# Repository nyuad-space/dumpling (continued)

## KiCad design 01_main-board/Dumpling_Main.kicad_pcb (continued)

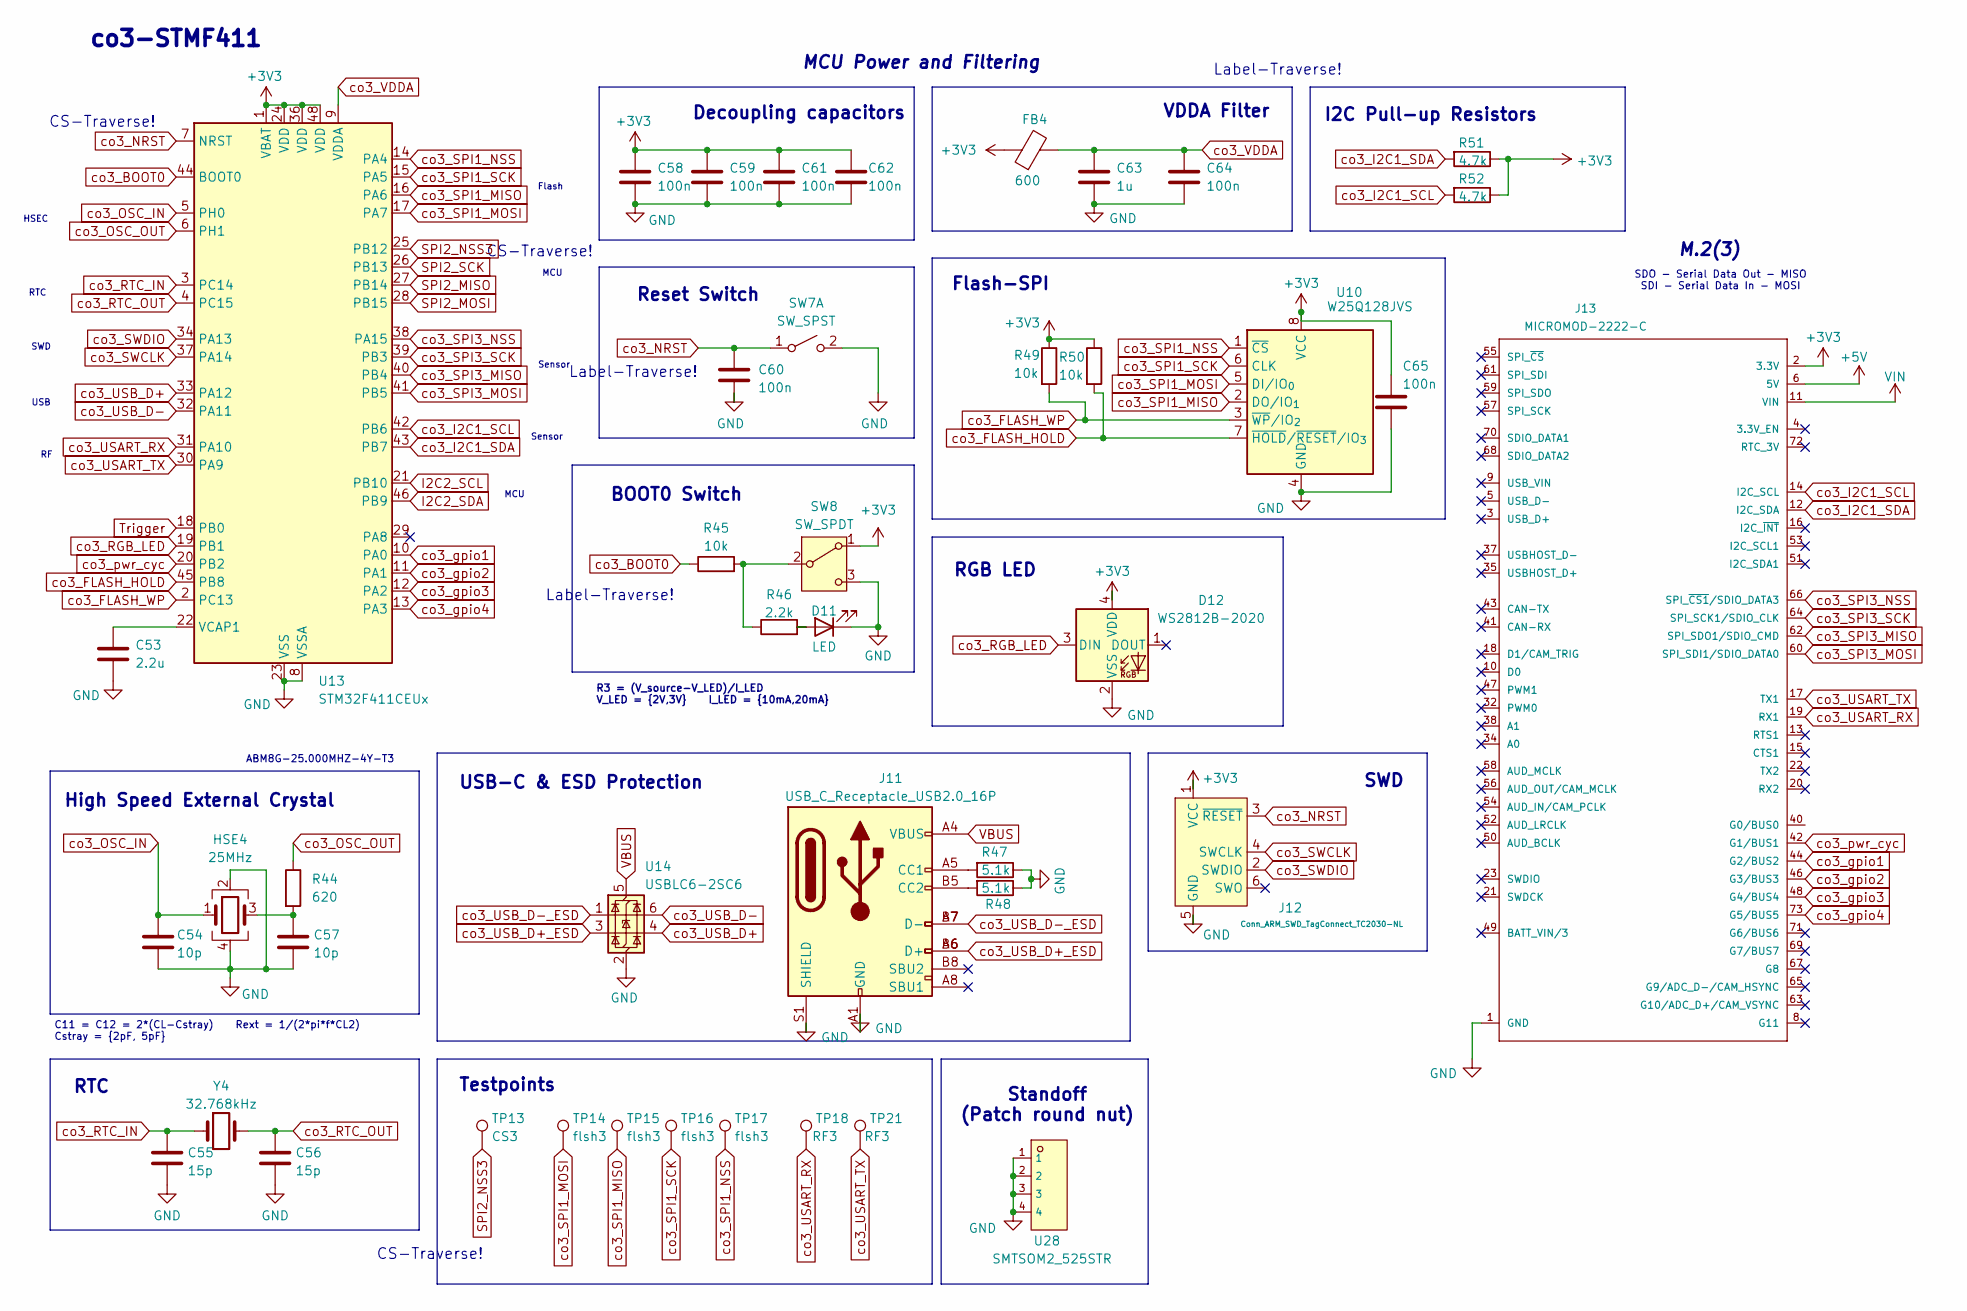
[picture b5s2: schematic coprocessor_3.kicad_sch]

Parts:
C53: 2.2u; C_0603_1608Metric
C54, C57: 10p; C_0402_1005Metric
C55, C56: 15p; C_0402_1005Metric
C58, C59, C60, C61, C62, C64, C65: 100n; C_0402_1005Metric
C63: 1u; C_0603_1608Metric
D11: LED; LED_0603_1608Metric
D12: WS2812B-2020; LED_WS2812B-2020_PLCC4_2.0x2.0mm
FB4: 600; L_0402_1005Metric
HSE4: 25MHz; Crystal_SMD_Abracon_ABM8G-4Pin_3.2x2.5mm
J11: USB_C_Receptacle_USB2.0_16P; USB_C_Receptacle_G-Switch_GT-USB-7051x
J12: Conn_ARM_SWD_TagConnect_TC2030-NL; Tag-Connect_TC2030-IDC-NL_2x03_P1.27mm_Vertical
J13: MICROMOD-2222-C; TE_2199119-4
R44: 620; R_0402_1005Metric
R45, R49, R50: 10k; R_0402_1005Metric
R46: 2.2k; R_0603_1608Metric
R47, R48: 5.1k; R_0402_1005Metric
R51, R52: 4.7k; R_0402_1005Metric
SW7: SW_SPST; SW_SPST_B3U-1000P
SW8: SW_SPDT; SW_JS102011JCQN
TP13: CS3; TestPoint_Pad_D1.0mm
TP14, TP15, TP16, TP17: flsh3; TestPoint_Pad_D1.0mm
TP18, TP21: RF3; TestPoint_Pad_D1.0mm
U10: W25Q128JVS; SOIC-8_5.3x5.3mm_P1.27mm
U13: STM32F411CEUx; QFN-48-1EP_7x7mm_P0.5mm_EP5.6x5.6mm
U14: USBLC6-2SC6; SOT-23-6
U28: SMTSOM2_525STR; SMD_BD5.6-D4.1; LCSC C22368605
Y4: 32.768kHz; Crystal_SMD_3215-2Pin_3.2x1.5mm

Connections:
+5V: J13.6 (5V); also elsewhere on the board
I2C2_SCL: U13.21 (PB10); also elsewhere on the board
I2C2_SDA: U13.46 (PB9); also elsewhere on the board
unnamed: C57.1, HSE4.3, R44.2
unnamed: D11.2 (A), R46.2
unnamed: J11.A5 (CC1), R47.2
unnamed: J11.B5 (CC2), R48.2
unnamed: R45.2, R46.1, SW8.2 (B)
unnamed: C53.1, U13.22 (VCAP1)
SPI2_MISO: U13.27 (PB14); also elsewhere on the board
SPI2_MOSI: U13.28 (PB15); also elsewhere on the board
SPI2_NSS3: TP13.1, U13.25 (PB12); also elsewhere on the board
SPI2_SCK: U13.26 (PB13); also elsewhere on the board
Trigger: U13.18 (PB0); also elsewhere on the board
VBUS: J11.A4 (VBUS), J11.A9 (VBUS), J11.B4 (VBUS), J11.B9 (VBUS), U14.5 (VBUS); also elsewhere on the board
VIN: J13.11 (VIN); also elsewhere on the board
co3_BOOT0: R45.1, U13.44 (BOOT0)
co3_FLASH_HOLD: R50.2, U10.7 (~HOLD/~RESET/IO_{3}), U13.45 (PB8)
co3_FLASH_WP: R49.2, U10.3 (~WP/IO_{2}), U13.2 (PC13)
co3_I2C1_SCL: J13.14 (I2C_SCL), R52.2, U13.42 (PB6)
co3_I2C1_SDA: J13.12 (I2C_SDA), R51.2, U13.43 (PB7)
co3_NRST: C60.1, J12.3 (~RESET), SW7.1 (A), U13.7 (NRST); also elsewhere on the board
co3_OSC_IN: C54.1, HSE4.1, U13.5 (PH0)
co3_OSC_OUT: R44.1, U13.6 (PH1)
co3_RGB_LED: D12.3 (DIN), U13.19 (PB1)
co3_RTC_IN: C55.1, U13.3 (PC14), Y4.1
co3_RTC_OUT: C56.1, U13.4 (PC15), Y4.2
co3_SPI1_MISO: TP15.1, U10.2 (DO/IO_{1}), U13.16 (PA6)
co3_SPI1_MOSI: TP14.1, U10.5 (DI/IO_{0}), U13.17 (PA7)
co3_SPI1_NSS: TP17.1, U10.1 (~CS), U13.14 (PA4)
co3_SPI1_SCK: TP16.1, U10.6 (CLK), U13.15 (PA5)
co3_SPI3_MISO: J13.62 (SPI_SDO1/SDIO_CMD), U13.40 (PB4)
co3_SPI3_MOSI: J13.60 (SPI_SDI1/SDIO_DATA0), U13.41 (PB5)
co3_SPI3_NSS: J13.66 (SPI_~CS1/SDIO_DATA3), U13.38 (PA15)
co3_SPI3_SCK: J13.64 (SPI_SCK1/SDIO_CLK), U13.39 (PB3)
co3_SWCLK: J12.4 (SWCLK), U13.37 (PA14)
co3_SWDIO: J12.2 (SWDIO), U13.34 (PA13)
co3_USART_RX: J13.19 (RX1), TP18.1, U13.31 (PA10)
co3_USART_TX: J13.17 (TX1), TP21.1, U13.30 (PA9)
co3_USB_D+: U13.33 (PA12), U14.4 (I/O2)
co3_USB_D+_ESD: J11.A6 (D+), J11.B6 (D+), U14.3 (I/O2)
co3_USB_D-: U13.32 (PA11), U14.6 (I/O1)
co3_USB_D-_ESD: J11.A7 (D-), J11.B7 (D-), U14.1 (I/O1)
co3_VDDA: C63.1, C64.1, FB4.2, U13.9 (VDDA)
co3_gpio1: J13.44 (G2/BUS2), U13.10 (PA0)
co3_gpio2: J13.46 (G3/BUS3), U13.11 (PA1)
co3_gpio3: J13.48 (G4/BUS4), U13.12 (PA2)
co3_gpio4: J13.73 (G5/BUS5), U13.13 (PA3)
co3_pwr_cyc: J13.42 (G1/BUS1), U13.20 (PB2)

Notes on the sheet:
Sensor
co3-STMF411
USB
Label-Traverse!
CS-Traverse!
SWD
Decoupling capacitors
Testpoints
C11 = C12 = 2*(CL-Cstray) Rext = 1/(2*pi*f*CL2) Cstray = {2pF, 5pF}
HSEC
Flash-SPI
BOOT0 Switch
Reset Switch
I2C Pull-up Resistors
VDDA Filter
High Speed External Crystal
M.2(3)
Standoff (Patch round nut)
SWD
Flash
MCU
RGB LED
ABM8G-25.000MHZ-4Y-T3
MCU Power and Filtering
SDO - Serial Data Out - MISO SDI - Serial Data In - MOSI
R3 = (V_source-V_LED)/I_LED V_LED = {2V,3V} I_LED = {10mA,20mA}
RTC
RTC
USB-C & ESD Protection

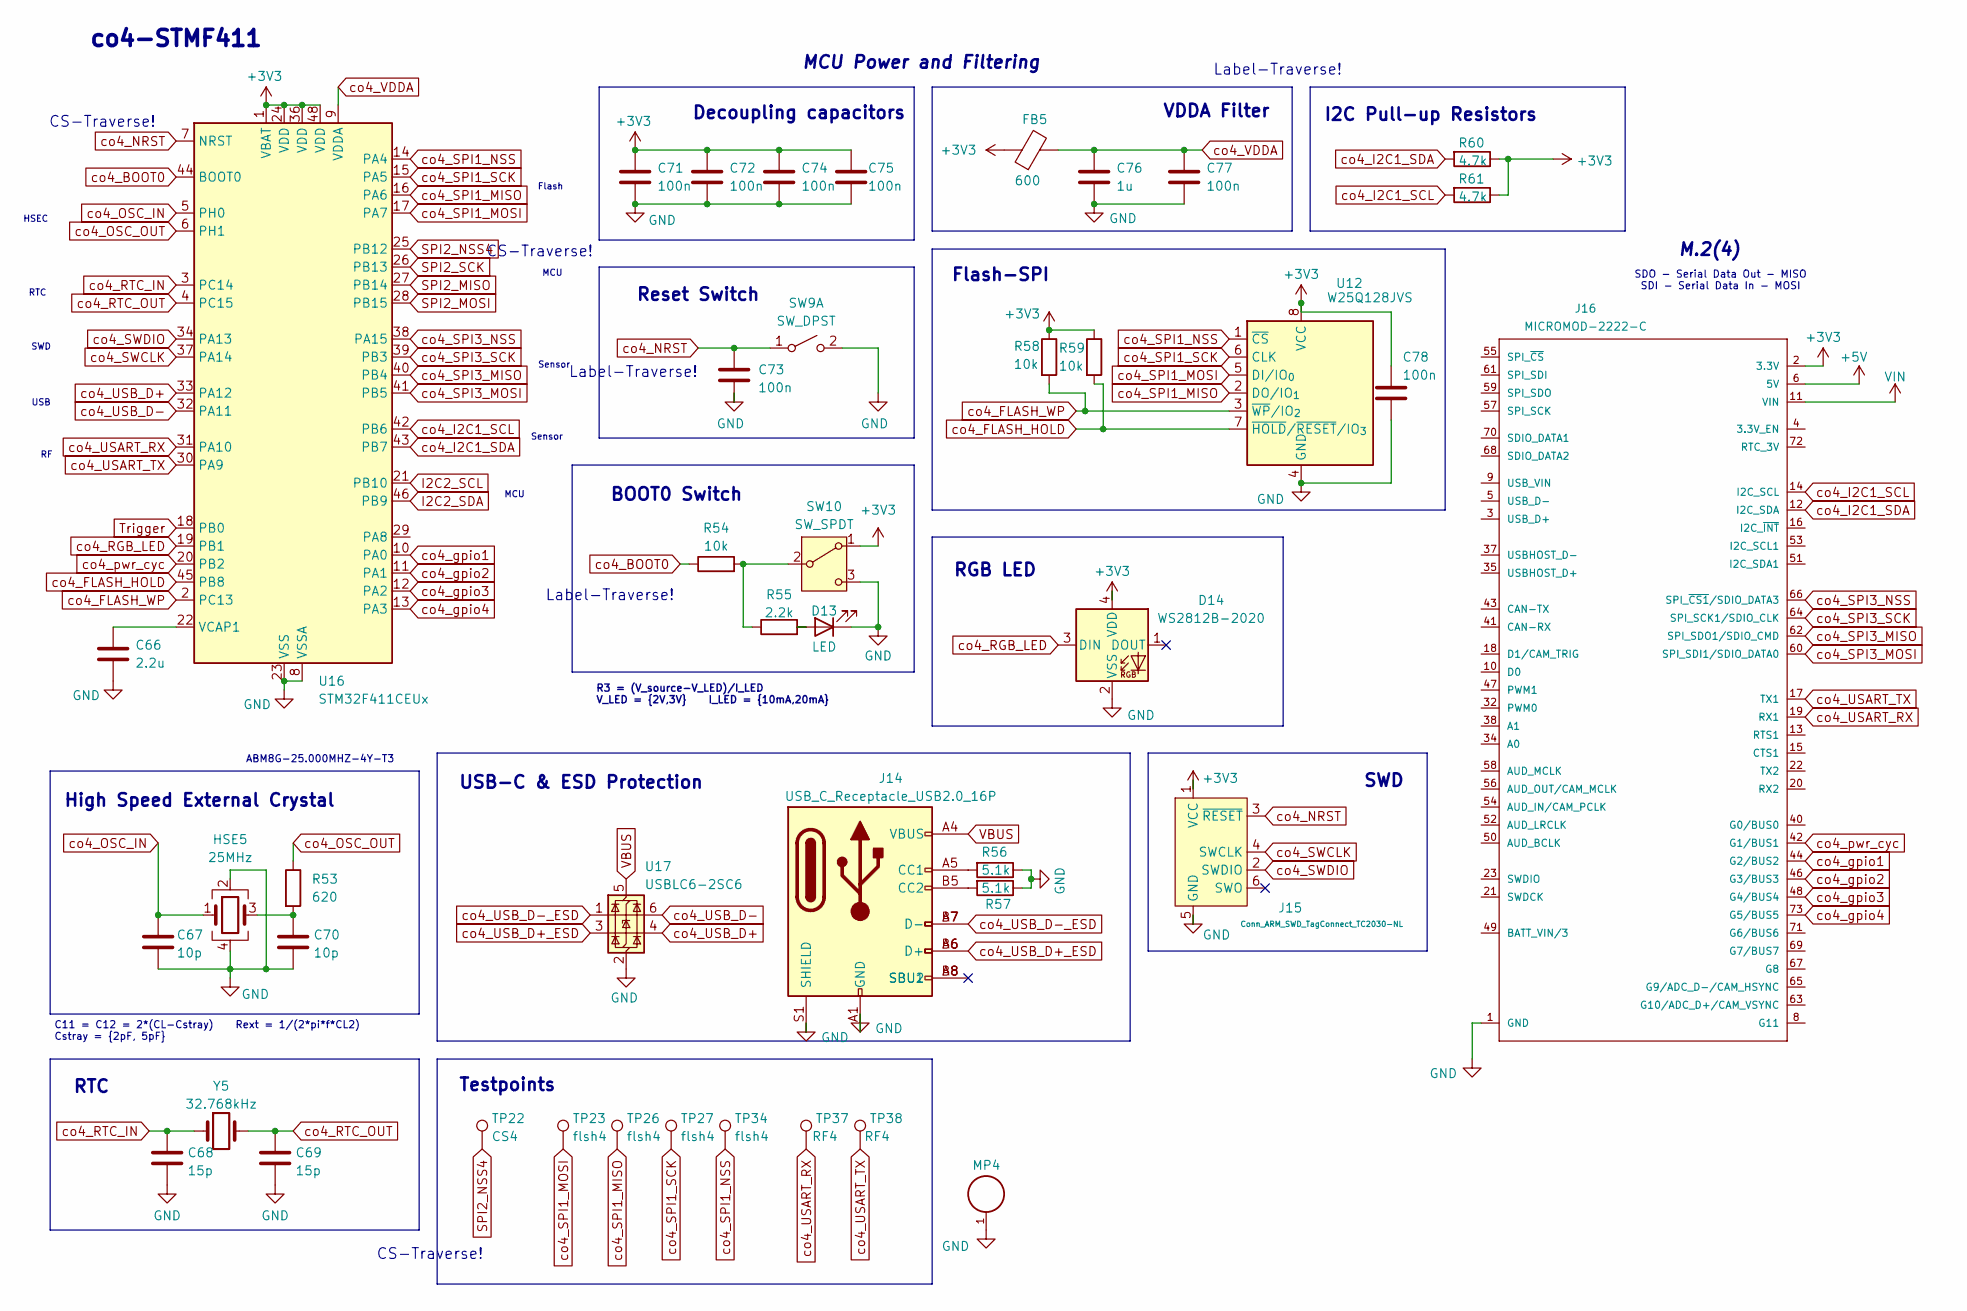
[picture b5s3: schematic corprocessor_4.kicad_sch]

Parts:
C66: 2.2u; C_0603_1608Metric
C67, C70: 10p; C_0402_1005Metric
C68, C69: 15p; C_0402_1005Metric
C71, C72, C73, C74, C75, C77, C78: 100n; C_0402_1005Metric
C76: 1u; C_0603_1608Metric
D13: LED; LED_0603_1608Metric
D14: WS2812B-2020; LED_WS2812B-2020_PLCC4_2.0x2.0mm
FB5: 600; L_0402_1005Metric
HSE5: 25MHz; Crystal_SMD_Abracon_ABM8G-4Pin_3.2x2.5mm
J14: USB_C_Receptacle_USB2.0_16P; USB_C_Receptacle_G-Switch_GT-USB-7051x
J15: Conn_ARM_SWD_TagConnect_TC2030-NL; Tag-Connect_TC2030-IDC-NL_2x03_P1.27mm_Vertical
J16: MICROMOD-2222-C; TE_2199119-4
MP4: WA-SMSI_9774025151; PART-NUMBER 9774025151R
R53: 620; R_0402_1005Metric
R54, R58, R59: 10k; R_0402_1005Metric
R55: 2.2k; R_0603_1608Metric
R56, R57: 5.1k; R_0402_1005Metric
R60, R61: 4.7k; R_0402_1005Metric
SW9: SW_DPST; SW_SPST_B3U-1000P
SW10: SW_SPDT; SW_CJS-1200TA
TP22: CS4; TestPoint_Pad_D1.0mm
TP23, TP26, TP27, TP34: flsh4; TestPoint_Pad_D1.0mm
TP37, TP38: RF4; TestPoint_Pad_D1.0mm
U12: W25Q128JVS; SOIC-8_5.3x5.3mm_P1.27mm
U16: STM32F411CEUx; QFN-48-1EP_7x7mm_P0.5mm_EP5.6x5.6mm
U17: USBLC6-2SC6; SOT-23-6
Y5: 32.768kHz; Crystal_SMD_3215-2Pin_3.2x1.5mm

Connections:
+5V: J16.6 (5V); also elsewhere on the board
I2C2_SCL: U16.21 (PB10); also elsewhere on the board
I2C2_SDA: U16.46 (PB9); also elsewhere on the board
unnamed: C70.1, HSE5.3, R53.2
unnamed: D13.2 (A), R55.2
unnamed: J14.A5 (CC1), R56.2
unnamed: J14.B5 (CC2), R57.2
unnamed: R54.2, R55.1, SW10.2 (B)
unnamed: C66.1, U16.22 (VCAP1)
SPI2_MISO: U16.27 (PB14); also elsewhere on the board
SPI2_MOSI: U16.28 (PB15); also elsewhere on the board
SPI2_NSS4: TP22.1, U16.25 (PB12); also elsewhere on the board
SPI2_SCK: U16.26 (PB13); also elsewhere on the board
Trigger: U16.18 (PB0); also elsewhere on the board
VBUS: J14.A4 (VBUS), J14.A9 (VBUS), J14.B4 (VBUS), J14.B9 (VBUS), U17.5 (VBUS); also elsewhere on the board
VIN: J16.11 (VIN); also elsewhere on the board
co4_BOOT0: R54.1, U16.44 (BOOT0)
co4_FLASH_HOLD: R59.2, U12.7 (~HOLD/~RESET/IO_{3}), U16.45 (PB8)
co4_FLASH_WP: R58.2, U12.3 (~WP/IO_{2}), U16.2 (PC13)
co4_I2C1_SCL: J16.14 (I2C_SCL), R61.2, U16.42 (PB6)
co4_I2C1_SDA: J16.12 (I2C_SDA), R60.2, U16.43 (PB7)
co4_NRST: C73.1, J15.3 (~RESET), SW9.1 (A), U16.7 (NRST); also elsewhere on the board
co4_OSC_IN: C67.1, HSE5.1, U16.5 (PH0)
co4_OSC_OUT: R53.1, U16.6 (PH1)
co4_RGB_LED: D14.3 (DIN), U16.19 (PB1)
co4_RTC_IN: C68.1, U16.3 (PC14), Y5.1
co4_RTC_OUT: C69.1, U16.4 (PC15), Y5.2
co4_SPI1_MISO: TP26.1, U12.2 (DO/IO_{1}), U16.16 (PA6)
co4_SPI1_MOSI: TP23.1, U12.5 (DI/IO_{0}), U16.17 (PA7)
co4_SPI1_NSS: TP34.1, U12.1 (~CS), U16.14 (PA4)
co4_SPI1_SCK: TP27.1, U12.6 (CLK), U16.15 (PA5)
co4_SPI3_MISO: J16.62 (SPI_SDO1/SDIO_CMD), U16.40 (PB4)
co4_SPI3_MOSI: J16.60 (SPI_SDI1/SDIO_DATA0), U16.41 (PB5)
co4_SPI3_NSS: J16.66 (SPI_~CS1/SDIO_DATA3), U16.38 (PA15)
co4_SPI3_SCK: J16.64 (SPI_SCK1/SDIO_CLK), U16.39 (PB3)
co4_SWCLK: J15.4 (SWCLK), U16.37 (PA14)
co4_SWDIO: J15.2 (SWDIO), U16.34 (PA13)
co4_USART_RX: J16.19 (RX1), TP37.1, U16.31 (PA10)
co4_USART_TX: J16.17 (TX1), TP38.1, U16.30 (PA9)
co4_USB_D+: U16.33 (PA12), U17.4 (I/O2)
co4_USB_D+_ESD: J14.A6 (D+), J14.B6 (D+), U17.3 (I/O2)
co4_USB_D-: U16.32 (PA11), U17.6 (I/O1)
co4_USB_D-_ESD: J14.A7 (D-), J14.B7 (D-), U17.1 (I/O1)
co4_VDDA: C76.1, C77.1, FB5.2, U16.9 (VDDA)
co4_gpio1: J16.44 (G2/BUS2), U16.10 (PA0)
co4_gpio2: J16.46 (G3/BUS3), U16.11 (PA1)
co4_gpio3: J16.48 (G4/BUS4), U16.12 (PA2)
co4_gpio4: J16.73 (G5/BUS5), U16.13 (PA3)
co4_pwr_cyc: J16.42 (G1/BUS1), U16.20 (PB2)

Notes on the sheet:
MCU
RTC
Testpoints
USB
Sensor
M.2(4)
USB-C & ESD Protection
HSEC
MCU Power and Filtering
Label-Traverse!
VDDA Filter
RTC
RGB LED
I2C Pull-up Resistors
C11 = C12 = 2*(CL-Cstray) Rext = 1/(2*pi*f*CL2) Cstray = {2pF, 5pF}
co4-STMF411
Flash
Reset Switch
R3 = (V_source-V_LED)/I_LED V_LED = {2V,3V} I_LED = {10mA,20mA}
CS-Traverse!
SWD
BOOT0 Switch
ABM8G-25.000MHZ-4Y-T3
SDO - Serial Data Out - MISO SDI - Serial Data In - MOSI
Decoupling capacitors
Flash-SPI
High Speed External Crystal
SWD

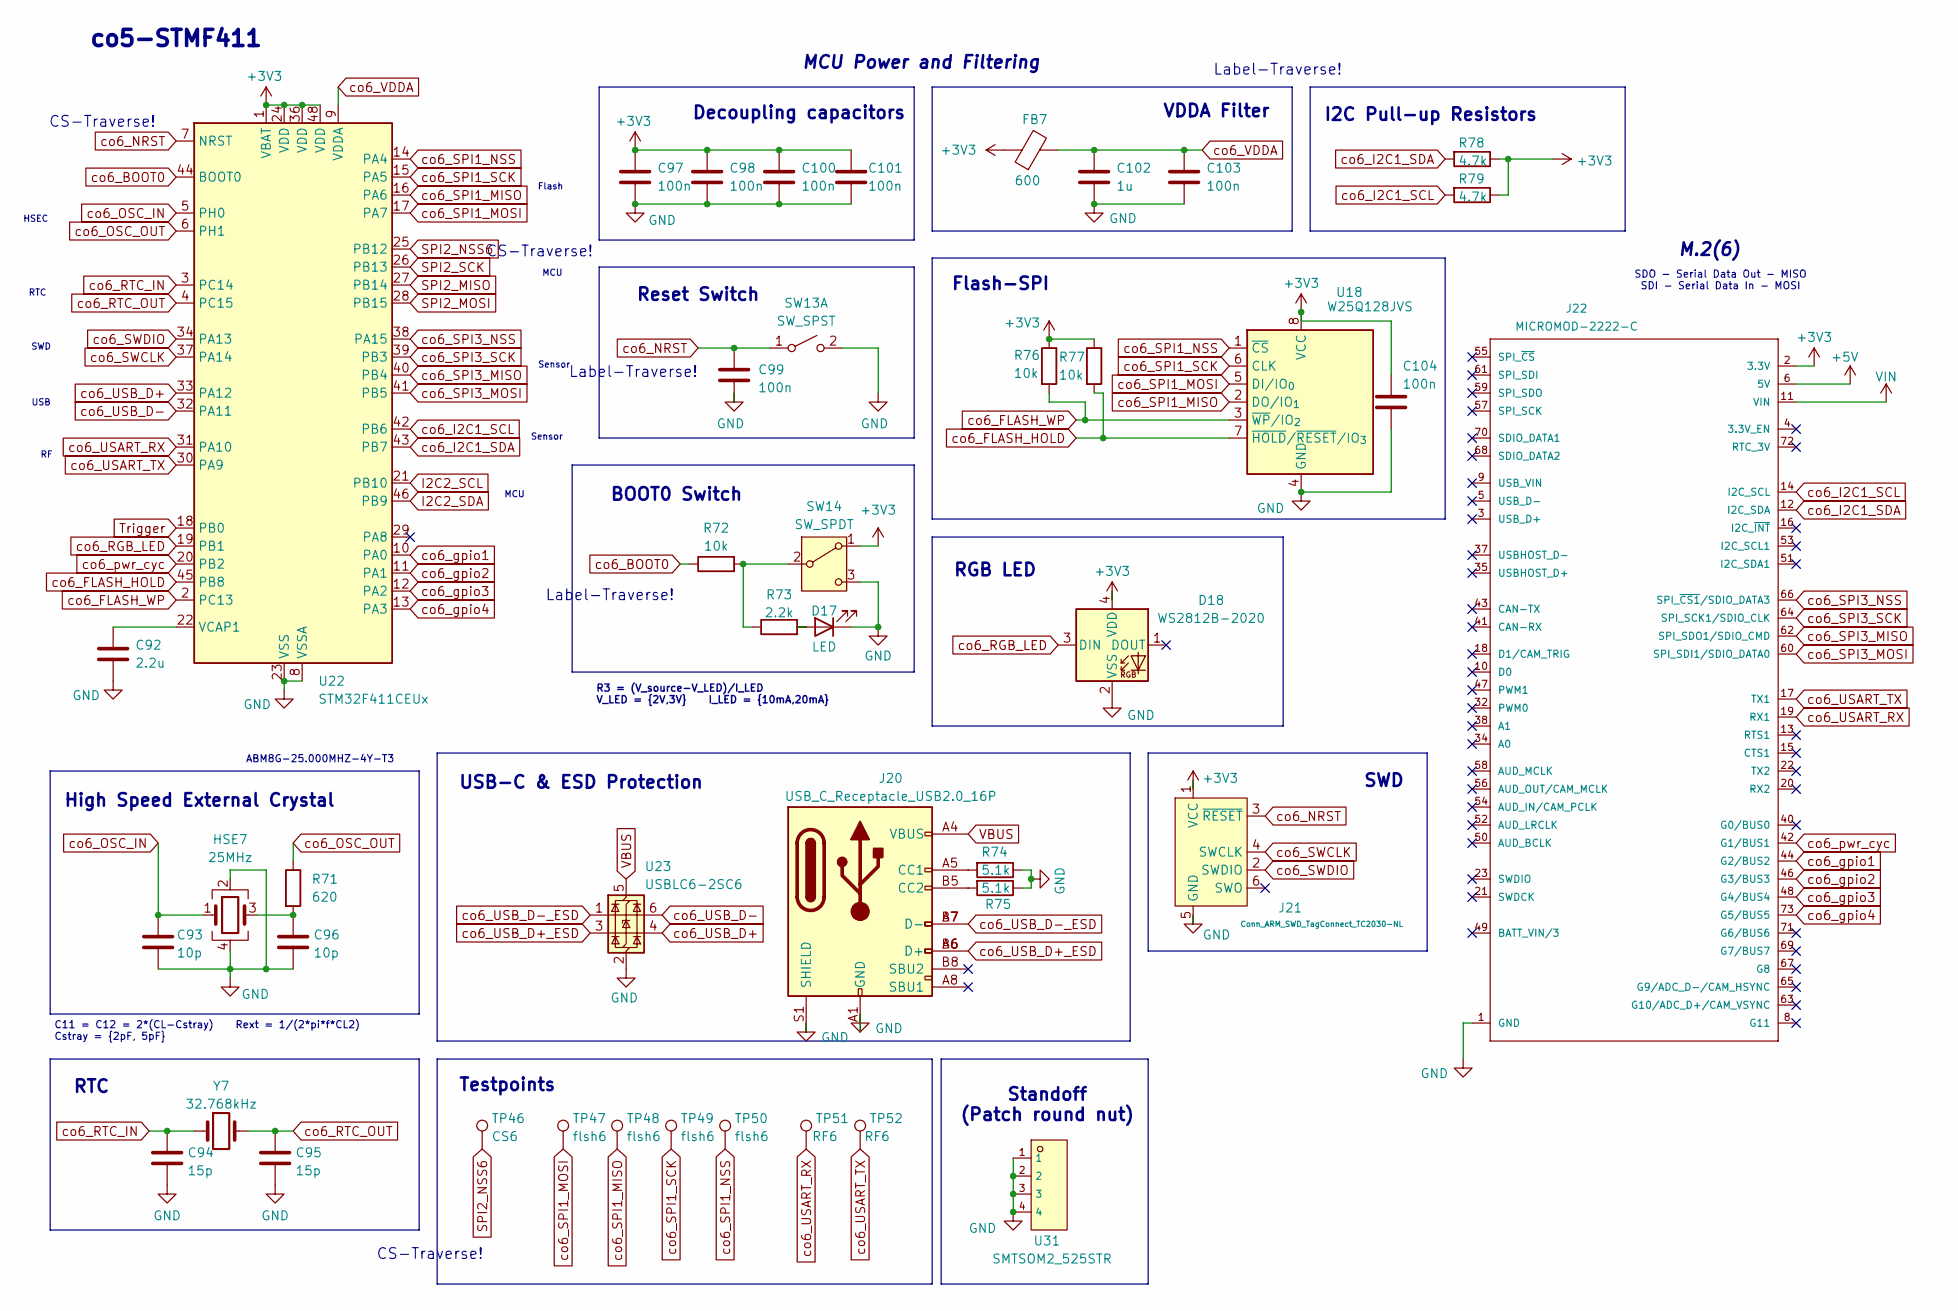
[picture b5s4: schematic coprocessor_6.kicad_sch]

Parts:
C92: 2.2u; C_0603_1608Metric
C93, C96: 10p; C_0402_1005Metric
C94, C95: 15p; C_0402_1005Metric
C97, C98, C99, C100, C101, C103, C104: 100n; C_0402_1005Metric
C102: 1u; C_0603_1608Metric
D17: LED; LED_0603_1608Metric
D18: WS2812B-2020; LED_WS2812B-2020_PLCC4_2.0x2.0mm
FB7: 600; L_0402_1005Metric
HSE7: 25MHz; Crystal_SMD_Abracon_ABM8G-4Pin_3.2x2.5mm
J20: USB_C_Receptacle_USB2.0_16P; USB_C_Receptacle_G-Switch_GT-USB-7051x
J21: Conn_ARM_SWD_TagConnect_TC2030-NL; Tag-Connect_TC2030-IDC-NL_2x03_P1.27mm_Vertical
J22: MICROMOD-2222-C; TE_2199119-4
R71: 620; R_0402_1005Metric
R72, R76, R77: 10k; R_0402_1005Metric
R73: 2.2k; R_0603_1608Metric
R74, R75: 5.1k; R_0402_1005Metric
R78, R79: 4.7k; R_0402_1005Metric
SW13: SW_SPST; SW_SPST_B3U-1000P
SW14: SW_SPDT; SW_JS102011JCQN
TP46: CS6; TestPoint_Pad_D1.0mm
TP47, TP48, TP49, TP50: flsh6; TestPoint_Pad_D1.0mm
TP51, TP52: RF6; TestPoint_Pad_D1.0mm
U18: W25Q128JVS; SOIC-8_5.3x5.3mm_P1.27mm
U22: STM32F411CEUx; QFN-48-1EP_7x7mm_P0.5mm_EP5.6x5.6mm
U23: USBLC6-2SC6; SOT-23-6
U31: SMTSOM2_525STR; SMD_BD5.6-D4.1; LCSC C22368605
Y7: 32.768kHz; Crystal_SMD_3215-2Pin_3.2x1.5mm

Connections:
+5V: J22.6 (5V); also elsewhere on the board
I2C2_SCL: U22.21 (PB10); also elsewhere on the board
I2C2_SDA: U22.46 (PB9); also elsewhere on the board
unnamed: C96.1, HSE7.3, R71.2
unnamed: D17.2 (A), R73.2
unnamed: J20.A5 (CC1), R74.2
unnamed: J20.B5 (CC2), R75.2
unnamed: R72.2, R73.1, SW14.2 (B)
unnamed: C92.1, U22.22 (VCAP1)
SPI2_MISO: U22.27 (PB14); also elsewhere on the board
SPI2_MOSI: U22.28 (PB15); also elsewhere on the board
SPI2_NSS6: TP46.1, U22.25 (PB12); also elsewhere on the board
SPI2_SCK: U22.26 (PB13); also elsewhere on the board
Trigger: U22.18 (PB0); also elsewhere on the board
VBUS: J20.A4 (VBUS), J20.A9 (VBUS), J20.B4 (VBUS), J20.B9 (VBUS), U23.5 (VBUS); also elsewhere on the board
VIN: J22.11 (VIN); also elsewhere on the board
co6_BOOT0: R72.1, U22.44 (BOOT0)
co6_FLASH_HOLD: R77.2, U18.7 (~HOLD/~RESET/IO_{3}), U22.45 (PB8)
co6_FLASH_WP: R76.2, U18.3 (~WP/IO_{2}), U22.2 (PC13)
co6_I2C1_SCL: J22.14 (I2C_SCL), R79.2, U22.42 (PB6)
co6_I2C1_SDA: J22.12 (I2C_SDA), R78.2, U22.43 (PB7)
co6_NRST: C99.1, J21.3 (~RESET), SW13.1 (A), U22.7 (NRST); also elsewhere on the board
co6_OSC_IN: C93.1, HSE7.1, U22.5 (PH0)
co6_OSC_OUT: R71.1, U22.6 (PH1)
co6_RGB_LED: D18.3 (DIN), U22.19 (PB1)
co6_RTC_IN: C94.1, U22.3 (PC14), Y7.1
co6_RTC_OUT: C95.1, U22.4 (PC15), Y7.2
co6_SPI1_MISO: TP48.1, U18.2 (DO/IO_{1}), U22.16 (PA6)
co6_SPI1_MOSI: TP47.1, U18.5 (DI/IO_{0}), U22.17 (PA7)
co6_SPI1_NSS: TP50.1, U18.1 (~CS), U22.14 (PA4)
co6_SPI1_SCK: TP49.1, U18.6 (CLK), U22.15 (PA5)
co6_SPI3_MISO: J22.62 (SPI_SDO1/SDIO_CMD), U22.40 (PB4)
co6_SPI3_MOSI: J22.60 (SPI_SDI1/SDIO_DATA0), U22.41 (PB5)
co6_SPI3_NSS: J22.66 (SPI_~CS1/SDIO_DATA3), U22.38 (PA15)
co6_SPI3_SCK: J22.64 (SPI_SCK1/SDIO_CLK), U22.39 (PB3)
co6_SWCLK: J21.4 (SWCLK), U22.37 (PA14)
co6_SWDIO: J21.2 (SWDIO), U22.34 (PA13)
co6_USART_RX: J22.19 (RX1), TP51.1, U22.31 (PA10)
co6_USART_TX: J22.17 (TX1), TP52.1, U22.30 (PA9)
co6_USB_D+: U22.33 (PA12), U23.4 (I/O2)
co6_USB_D+_ESD: J20.A6 (D+), J20.B6 (D+), U23.3 (I/O2)
co6_USB_D-: U22.32 (PA11), U23.6 (I/O1)
co6_USB_D-_ESD: J20.A7 (D-), J20.B7 (D-), U23.1 (I/O1)
co6_VDDA: C102.1, C103.1, FB7.2, U22.9 (VDDA)
co6_gpio1: J22.44 (G2/BUS2), U22.10 (PA0)
co6_gpio2: J22.46 (G3/BUS3), U22.11 (PA1)
co6_gpio3: J22.48 (G4/BUS4), U22.12 (PA2)
co6_gpio4: J22.73 (G5/BUS5), U22.13 (PA3)
co6_pwr_cyc: J22.42 (G1/BUS1), U22.20 (PB2)

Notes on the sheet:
R3 = (V_source-V_LED)/I_LED V_LED = {2V,3V} I_LED = {10mA,20mA}
HSEC
USB-C & ESD Protection
ABM8G-25.000MHZ-4Y-T3
C11 = C12 = 2*(CL-Cstray) Rext = 1/(2*pi*f*CL2) Cstray = {2pF, 5pF}
Sensor
Label-Traverse!
BOOT0 Switch
SDO - Serial Data Out - MISO SDI - Serial Data In - MOSI
CS-Traverse!
Decoupling capacitors
Reset Switch
Flash
MCU
USB
RGB LED
High Speed External Crystal
SWD
co5-STMF411
I2C Pull-up Resistors
VDDA Filter
M.2(6)
RTC
MCU Power and Filtering
Standoff (Patch round nut)
Flash-SPI
SWD
Testpoints
RTC

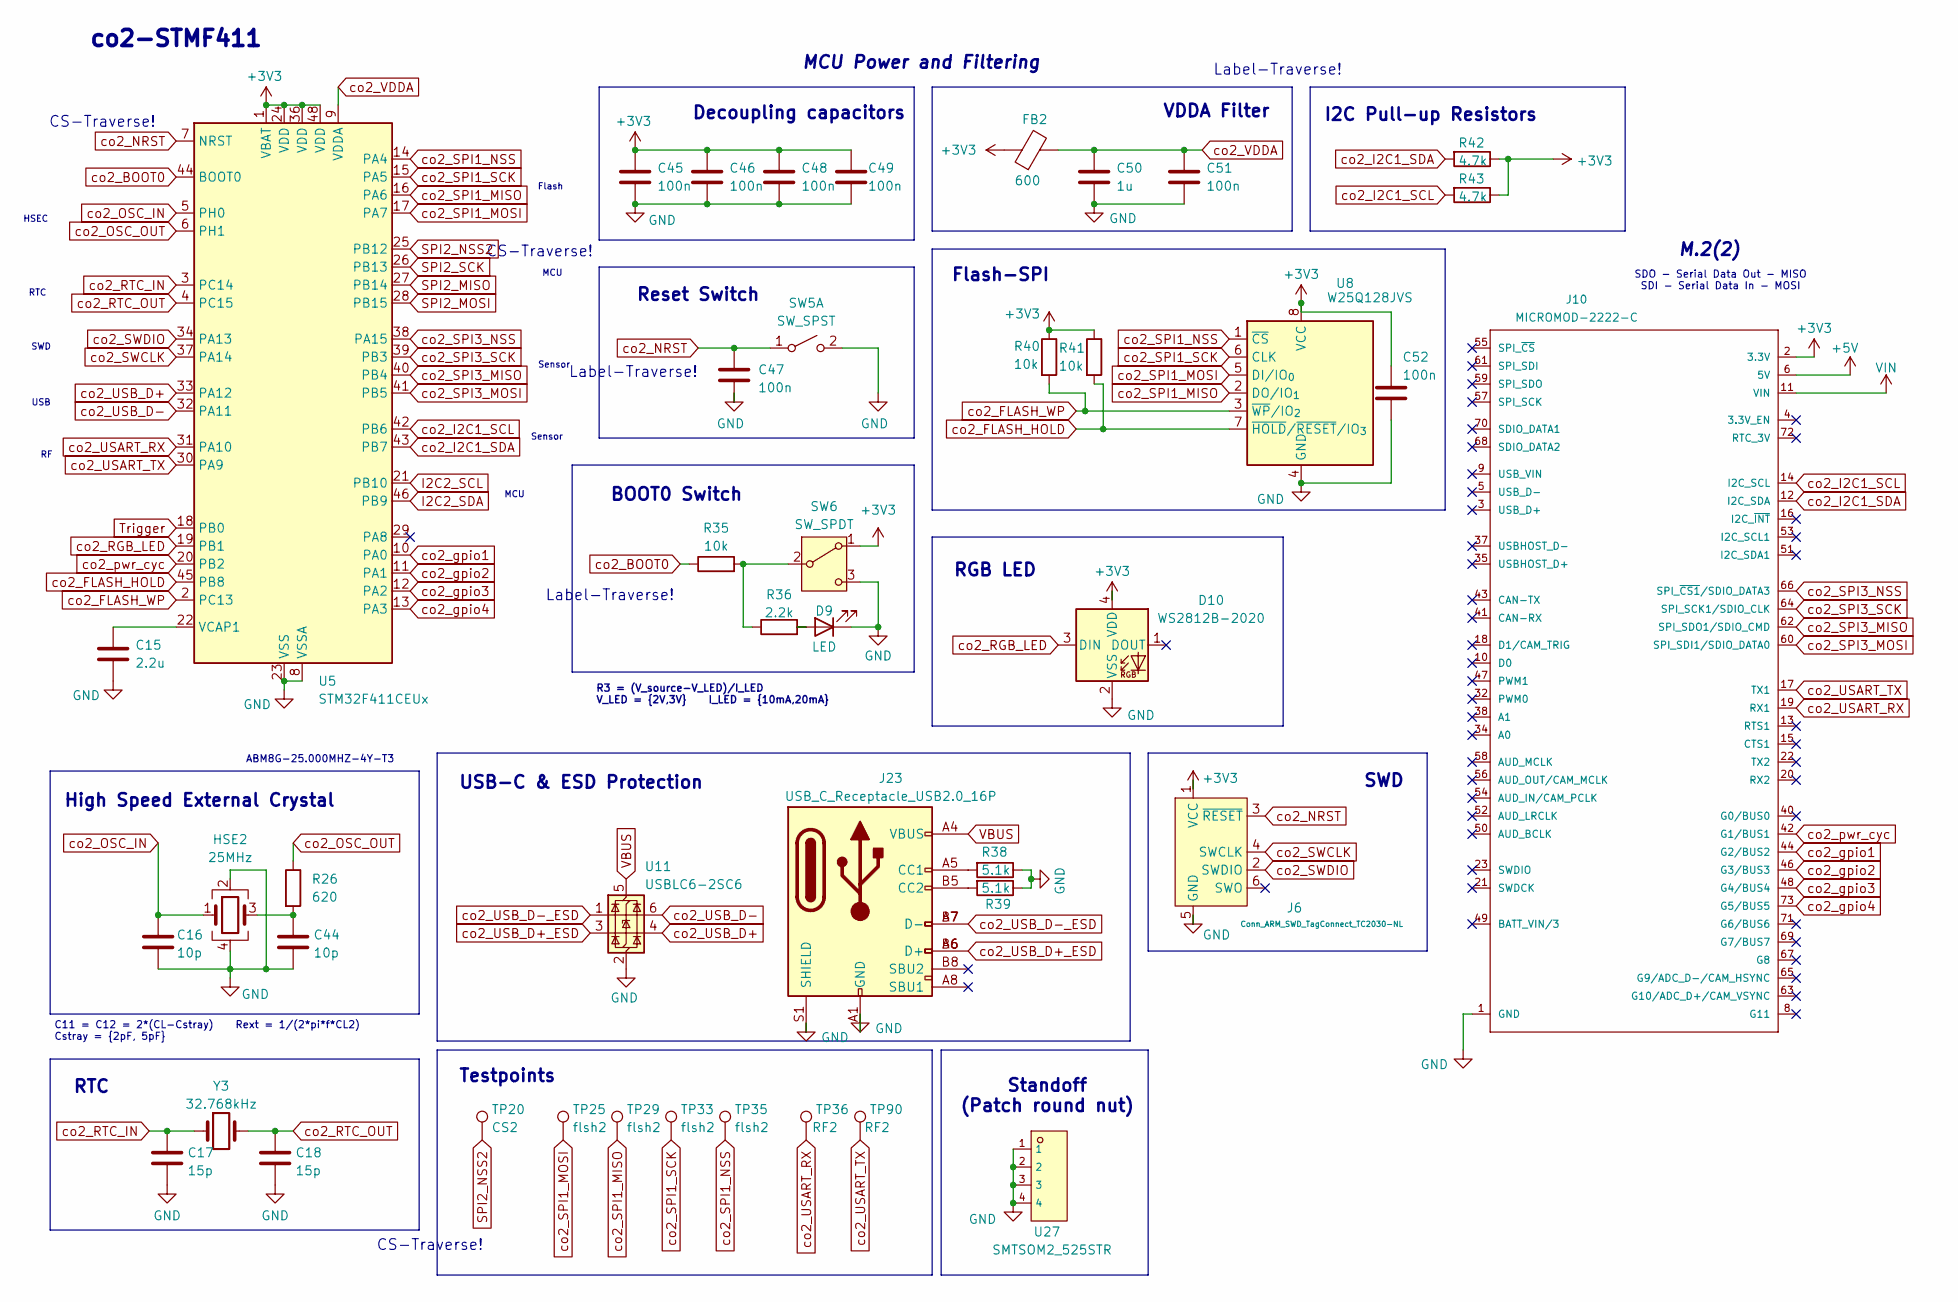
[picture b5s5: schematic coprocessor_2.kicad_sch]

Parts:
C15: 2.2u; C_0603_1608Metric
C16, C44: 10p; C_0402_1005Metric
C17, C18: 15p; C_0402_1005Metric
C45, C46, C47, C48, C49, C51, C52: 100n; C_0402_1005Metric
C50: 1u; C_0603_1608Metric
D9: LED; LED_0603_1608Metric
D10: WS2812B-2020; LED_WS2812B-2020_PLCC4_2.0x2.0mm
FB2: 600; L_0402_1005Metric
HSE2: 25MHz; Crystal_SMD_Abracon_ABM8G-4Pin_3.2x2.5mm
J6: Conn_ARM_SWD_TagConnect_TC2030-NL; Tag-Connect_TC2030-IDC-NL_2x03_P1.27mm_Vertical
J10: MICROMOD-2222-C; TE_2199119-4
J23: USB_C_Receptacle_USB2.0_16P; USB_C_Receptacle_G-Switch_GT-USB-7051x
R26: 620; R_0402_1005Metric
R35, R40, R41: 10k; R_0402_1005Metric
R36: 2.2k; R_0603_1608Metric
R38, R39: 5.1k; R_0402_1005Metric
R42, R43: 4.7k; R_0402_1005Metric
SW5: SW_SPST; SW_SPST_B3U-1000P
SW6: SW_SPDT; SW_JS102011JCQN
TP20: CS2; TestPoint_Pad_D1.0mm
TP25, TP29, TP33, TP35: flsh2; TestPoint_Pad_D1.0mm
TP36, TP90: RF2; TestPoint_Pad_D1.0mm
U5: STM32F411CEUx; QFN-48-1EP_7x7mm_P0.5mm_EP5.6x5.6mm
U8: W25Q128JVS; SOIC-8_5.3x5.3mm_P1.27mm
U11: USBLC6-2SC6; SOT-23-6
U27: SMTSOM2_525STR; SMD_BD5.6-D4.1; LCSC C22368605
Y3: 32.768kHz; Crystal_SMD_3215-2Pin_3.2x1.5mm

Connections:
+5V: J10.6 (5V); also elsewhere on the board
I2C2_SCL: U5.21 (PB10); also elsewhere on the board
I2C2_SDA: U5.46 (PB9); also elsewhere on the board
unnamed: C44.1, HSE2.3, R26.2
unnamed: D9.2 (A), R36.2
unnamed: J23.A5 (CC1), R38.2
unnamed: J23.B5 (CC2), R39.2
unnamed: R35.2, R36.1, SW6.2 (B)
unnamed: C15.1, U5.22 (VCAP1)
SPI2_MISO: U5.27 (PB14); also elsewhere on the board
SPI2_MOSI: U5.28 (PB15); also elsewhere on the board
SPI2_NSS2: TP20.1, U5.25 (PB12); also elsewhere on the board
SPI2_SCK: U5.26 (PB13); also elsewhere on the board
Trigger: U5.18 (PB0); also elsewhere on the board
VBUS: J23.A4 (VBUS), J23.A9 (VBUS), J23.B4 (VBUS), J23.B9 (VBUS), U11.5 (VBUS); also elsewhere on the board
VIN: J10.11 (VIN); also elsewhere on the board
co2_BOOT0: R35.1, U5.44 (BOOT0)
co2_FLASH_HOLD: R41.2, U5.45 (PB8), U8.7 (~HOLD/~RESET/IO_{3})
co2_FLASH_WP: R40.2, U5.2 (PC13), U8.3 (~WP/IO_{2})
co2_I2C1_SCL: J10.14 (I2C_SCL), R43.2, U5.42 (PB6)
co2_I2C1_SDA: J10.12 (I2C_SDA), R42.2, U5.43 (PB7)
co2_NRST: C47.1, J6.3 (~RESET), SW5.1 (A), U5.7 (NRST); also elsewhere on the board
co2_OSC_IN: C16.1, HSE2.1, U5.5 (PH0)
co2_OSC_OUT: R26.1, U5.6 (PH1)
co2_RGB_LED: D10.3 (DIN), U5.19 (PB1)
co2_RTC_IN: C17.1, U5.3 (PC14), Y3.1
co2_RTC_OUT: C18.1, U5.4 (PC15), Y3.2
co2_SPI1_MISO: TP29.1, U5.16 (PA6), U8.2 (DO/IO_{1})
co2_SPI1_MOSI: TP25.1, U5.17 (PA7), U8.5 (DI/IO_{0})
co2_SPI1_NSS: TP35.1, U5.14 (PA4), U8.1 (~CS)
co2_SPI1_SCK: TP33.1, U5.15 (PA5), U8.6 (CLK)
co2_SPI3_MISO: J10.62 (SPI_SDO1/SDIO_CMD), U5.40 (PB4)
co2_SPI3_MOSI: J10.60 (SPI_SDI1/SDIO_DATA0), U5.41 (PB5)
co2_SPI3_NSS: J10.66 (SPI_~CS1/SDIO_DATA3), U5.38 (PA15)
co2_SPI3_SCK: J10.64 (SPI_SCK1/SDIO_CLK), U5.39 (PB3)
co2_SWCLK: J6.4 (SWCLK), U5.37 (PA14)
co2_SWDIO: J6.2 (SWDIO), U5.34 (PA13)
co2_USART_RX: J10.19 (RX1), TP36.1, U5.31 (PA10)
co2_USART_TX: J10.17 (TX1), TP90.1, U5.30 (PA9)
co2_USB_D+: U5.33 (PA12), U11.4 (I/O2)
co2_USB_D+_ESD: J23.A6 (D+), J23.B6 (D+), U11.3 (I/O2)
co2_USB_D-: U5.32 (PA11), U11.6 (I/O1)
co2_USB_D-_ESD: J23.A7 (D-), J23.B7 (D-), U11.1 (I/O1)
co2_VDDA: C50.1, C51.1, FB2.2, U5.9 (VDDA)
co2_gpio1: J10.44 (G2/BUS2), U5.10 (PA0)
co2_gpio2: J10.46 (G3/BUS3), U5.11 (PA1)
co2_gpio3: J10.48 (G4/BUS4), U5.12 (PA2)
co2_gpio4: J10.73 (G5/BUS5), U5.13 (PA3)
co2_pwr_cyc: J10.42 (G1/BUS1), U5.20 (PB2)

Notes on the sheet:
Label-Traverse!
RGB LED
Sensor
USB
VDDA Filter
SWD
HSEC
C11 = C12 = 2*(CL-Cstray) Rext = 1/(2*pi*f*CL2) Cstray = {2pF, 5pF}
CS-Traverse!
High Speed External Crystal
USB-C & ESD Protection
Flash-SPI
Testpoints
Standoff (Patch round nut)
R3 = (V_source-V_LED)/I_LED V_LED = {2V,3V} I_LED = {10mA,20mA}
SWD
RTC
Flash
Decoupling capacitors
RTC
Reset Switch
MCU
ABM8G-25.000MHZ-4Y-T3
MCU Power and Filtering
co2-STMF411
BOOT0 Switch
SDO - Serial Data Out - MISO SDI - Serial Data In - MOSI
M.2(2)
I2C Pull-up Resistors

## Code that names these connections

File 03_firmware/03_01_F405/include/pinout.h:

// Interboard SPI pins
#define INTERBOARD_SPI_SCK PB13
#define INTERBOARD_SPI_MISO PB14
#define INTERBOARD_SPI_MOSI PB15

#define INTERBOARD_SPI_CO1_CS PC3
#define INTERBOARD_SPI_CO2_CS PB12
#define INTERBOARD_SPI_CO3_CS PC2
#define INTERBOARD_SPI_CO4_CS PC6
#define INTERBOARD_SPI_CO5_CS PC4
#define INTERBOARD_SPI_CO6_CS PC5


// Flash SPI pins
#define FLASH_SPI_CS PA4
#define FLASH_SPI_SCK PA5
#define FLASH_SPI_MISO PA6
#define FLASH_SPI_MOSI PA7

// Log triger
#define LOG_TRIGGER_GPIO PC13

// MPU Pins
#define MPU_SCL PA8
#define MPU_SDA PC9
#define MPU_INT PA8

// Indicators
#define BUZZER PB8
#define RGB_LED PB9

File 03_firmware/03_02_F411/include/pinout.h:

// SPI bus (SPI3)
// Use ALT1 pin names to avoid SPI conflict. 
// This guarantees SENSOR_SPI will use SPI3, as expected.
#define SENSOR_SCK PB3_ALT1
#define SENSOR_MISO PB4_ALT1  
#define SENSOR_MOSI PB5_ALT1

// Sensor CS
#define SENSOR_CS PA15
#define LSM6DS_CS PA15
#define DPS310_CS PA15
#define BMI088_Accel_CS PA15
#define BMI088_Gyro_CS PA2

// SPI bus (SPI2)
#define INTERBOARD_CS PB12 // Dummy
#define INTERBOARD_SCK PB13
#define INTERBOARD_MISO PB14
#define INTERBOARD_MOSI PB15

// SPI bus (SPI1)
#define FLASH_CS PA4
#define FLASH_SCK PA5
#define FLASH_MISO PA6
#define FLASH_MOSI PA7

// I2C sensors (I2C1)
#define SENSOR_SCL PB6
#define SENSOR_SDA PB7

// Log triger
#define LOG_TRIGGER_GPIO PB0

// Indicator
#define RGB_LED PB1

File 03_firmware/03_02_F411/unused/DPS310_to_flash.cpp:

#include "main.h"
#include <Arduino.h>
#include <SPI.h>
#include <Adafruit_DPS310.h>
#include <SPIFlash.h>

// rid of LED, make more concise

// === DPS310 CONFIG ===
#define DPS310_CS PA15
#define DPS310_SCK PB3
#define DPS310_MISO PB4
#define DPS310_MOSI PB5

Adafruit_DPS310 dps;

// === FLASH CONFIG ===
#define FLASH_SS PA4 // Chip Select for SPI Flash (Winbond W25Q16 for example)
#define FLASH_SCK PA5
#define FLASH_MISO PB4
#define FLASH_MOSI PA7

SPIFlash flash(FLASH_SS, 0xEF30); // Change JEDEC ID to 0xEF40 for 16Mbit chips
uint32_t writeAddress = 0;        // Start writing at 0

// LED blink config
int LEDTIME = 500;

// Data struct for flash
struct SensorData
{
    float temperature;
    float pressure;
    uint32_t timestamp;
};

void setup()
{
    Serial.begin(115200);
    Serial.println("I'm Alive!");

    while (!Serial)
        delay(10);

    // === FLASH INIT ===
    flash.wakeup();
    if (flash.initialize())
    {
        Serial.println("SPI Flash Init OK!");
        LEDTIME = 1000; // Blink slow
    }
    else
    {
        Serial.println("SPI Flash Init FAIL! (is chip connected?)");
        LEDTIME = 100; // Blink fast
    }

    // === SENSOR INIT ===
    Serial.println("DPS310 init...");
    if (!dps.begin_SPI(DPS310_CS, DPS310_SCK, DPS310_MISO, DPS310_MOSI))
    {
        Serial.println("Failed to find DPS310 sensor");
        while (1)
            yield();
    }
    Serial.println("DPS310 OK");

    dps.configurePressure(DPS310_64HZ, DPS310_64SAMPLES);
    dps.configureTemperature(DPS310_64HZ, DPS310_64SAMPLES);
}

void loop()
{
    sensors_event_t temp_event, pressure_event;

    // Check if data is ready
    if (!dps.temperatureAvailable() || !dps.pressureAvailable())
    {
        delay(100);
        return;
    }

    dps.getEvents(&temp_event, &pressure_event);

    // Log to Serial
    Serial.print("Temp: ");
    Serial.print(temp_event.temperature);
    Serial.print(" *C | ");

    Serial.print("Pressure: ");
    Serial.print(pressure_event.pressure);
    Serial.println(" hPa");

    // Create data struct
    SensorData data;
    data.temperature = temp_event.temperature;
    data.pressure = pressure_event.pressure;
    data.timestamp = millis();

    // Write to flash
    flash.writeBytes(writeAddress, (uint8_t *)&data, sizeof(SensorData));
    Serial.print("Wrote to flash at address 0x");
    Serial.println(writeAddress, HEX);

    // Read back to verify
    SensorData verify;
    flash.readBytes(writeAddress, (uint8_t *)&verify, sizeof(SensorData));

    if (verify.temperature == data.temperature && verify.pressure == data.pressure)
    {
        Serial.println("Write verified!");
    }
    else
    {
        Serial.println("Verification failed.");
    }

    writeAddress += sizeof(SensorData);

    // Blink LED
    digitalWrite(LED_BUILTIN, HIGH);
    delay(LEDTIME / 2);
    digitalWrite(LED_BUILTIN, LOW);
    delay(LEDTIME / 2);
}

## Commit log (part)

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2024-11-28 added micromod library
2024-11-28 changed folder structure
2025-01-21 added mcu
2025-01-22 Added supporting circuitry
2025-03-10 added coprocessors
2025-03-10 layout
2025-03-10 dumped stuff away
2025-03-19 power routing
2025-03-31 wired
2025-03-31 wiring fin, pre-drc
2025-05-07 ebay backboard
2025-05-09 deleted files
2025-05-09 autosave deleted
2025-05-22 Added six sensorboards
2025-05-27 filled missing connections :/
2025-05-27 schematic pdf
2025-05-30 schematic update
2025-05-30 cleanup
2025-05-30 firmware update
2025-05-31 detect sensor, read sensor, write to local flash
2025-06-02 sensor config
2025-06-02 log sensor
2025-06-02 SPIPacket init
2025-06-02 F405 init
2025-06-02 add symlink to F411 ini
2025-06-03 wiped
2025-06-04 error in detectSensor
2025-06-05 sensor detection works
2025-06-06 sensor detect (w/o HDC302)
2025-06-06 Functioning sensor detect
2025-06-06 Better naming
2025-06-06 heartbeat with error
2025-06-06 Revert "heartbeat with error"
    This reverts commit fa3044730102aa221b6a0c8ac8d58779b8e22936.
2025-06-06 rename sensor objects for clarity
2025-06-07 init config sensors
2025-06-07 spi dev stuck
2025-06-07 Refactor sensor detect, don't use global objects
2025-06-08 Remove unused junk code
2025-06-08 Naming fix + remove includes
2025-06-08 Fix BMI CS names
2025-06-08 Fix var name
2025-06-08 Working comm init and sensor config
2025-06-08 Working SPI slave mode for coprocessor
2025-06-08 Remove extra lines
2025-06-08 init flash comm
2025-06-08 FIx SPI bus contention
2025-06-09 reads dps310
2025-06-09 reading lsm6
2025-06-09 reads bmp390
2025-06-09 reads bmi088
2025-06-09 sensor_read better format
2025-06-09 reads lsm6ds
2025-06-09 reads sensors
2025-06-09 reads lis2mdl, hdc302
2025-06-09 sensor read cleanup
2025-06-09 remove timestamp print
2025-06-09 variable name mismatch fix
2025-06-09 serial print added
2025-06-09 added flash init
2025-06-09 write sensor to flash (with errors)
2025-06-09 added writing to flash
2025-06-10 Flash write synced with sensor read
2025-06-10 Working flash read
2025-06-10 sensor_read format cleanup
2025-06-10 function name cleanup + read_from_flash reformat
2025-06-10 compare with request_size
2025-06-11 read from flash by chunks (with error)
2025-06-11 updated read flash functions
2025-06-11 read from flash + by chunks of requested size + return read buffer
2025-06-11 F405 flight and data collection logic
2025-06-11 More launch detect logic
2025-06-11 GPIO triggering on main
2025-06-11 Add debug statements
2025-06-11 Working two requests
2025-06-11 Flesh out main logic
2025-06-11 Fix debugging
2025-06-11 minor fix + debug macro
2025-06-11 fix debug statements
2025-06-11 Remove old readfromflash
2025-06-11 discard old header
2025-06-11 added clear flash function
2025-06-11 Fix input pullup state mistake
2025-06-11 Blink red on init failures
2025-06-11 Missing semicolon
2025-06-11 First entry in logic was useless
2025-06-11 Add comments to launch detection
2025-06-12 Don't get data again
2025-06-12 change trigger logic
2025-06-12 Additional logging
2025-06-12 Update params
2025-06-12 Set two thresholds
2025-06-12 change debug macro names, FAILING SPI comm
2025-06-12 Init logging logic
2025-06-12 circular buffer write+read
2025-06-12 circular buffer + handling flash clear
2025-06-12 readFlash returns buffer reading size
2025-06-12 Make data collection dummy, skip it.
2025-06-12 circular buffer + clear flash by debug
2025-06-15 up to stage fright flight
2025-06-16 combined opening file + writing header
2025-06-16 error in initializing/opening file
2025-06-16 working circular to regular logging
2025-06-16 refined detection logic and led states
2025-06-16 dev notes update
2025-06-19 more cleanup
2025-06-19 circular to regular tested
2025-06-19 added Run SdFat_format notice
2025-06-19 added delay, now reads both (bruh)
2025-06-19 flash debug and logic improved
2025-06-19 successful reading/wriitng to both files
2025-06-21 added variadic logStatus
2025-06-21 added logStatus statements
2025-06-22 successful read/write to status log file
2025-06-22 added F411 LED
2025-06-22 fixed HDC302 reading
2025-06-22 adjusted sensor config details + added status log statements
2025-08-02 added board renderings
2026-06-09 move to legacy
2026-06-09 added new pio
2026-06-09 added minimal LSM6DS + flash drivers
2026-06-10 added serial monitor/ flash log modes
2026-06-10 added buildflag + verified one sensor log/dump pipeline
2026-06-11 added host-side dashboard_app
2026-06-12 added live/playback modes + export downloader in app
2026-06-27 separated flash begin for read-only + cleaned operating modes
